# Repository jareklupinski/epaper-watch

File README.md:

# epaper-watch
An epaper watch with a minimalist design and UI

I was working on the breakout board and library for a round epaper display went I accidentally the whole thing.

Oops.

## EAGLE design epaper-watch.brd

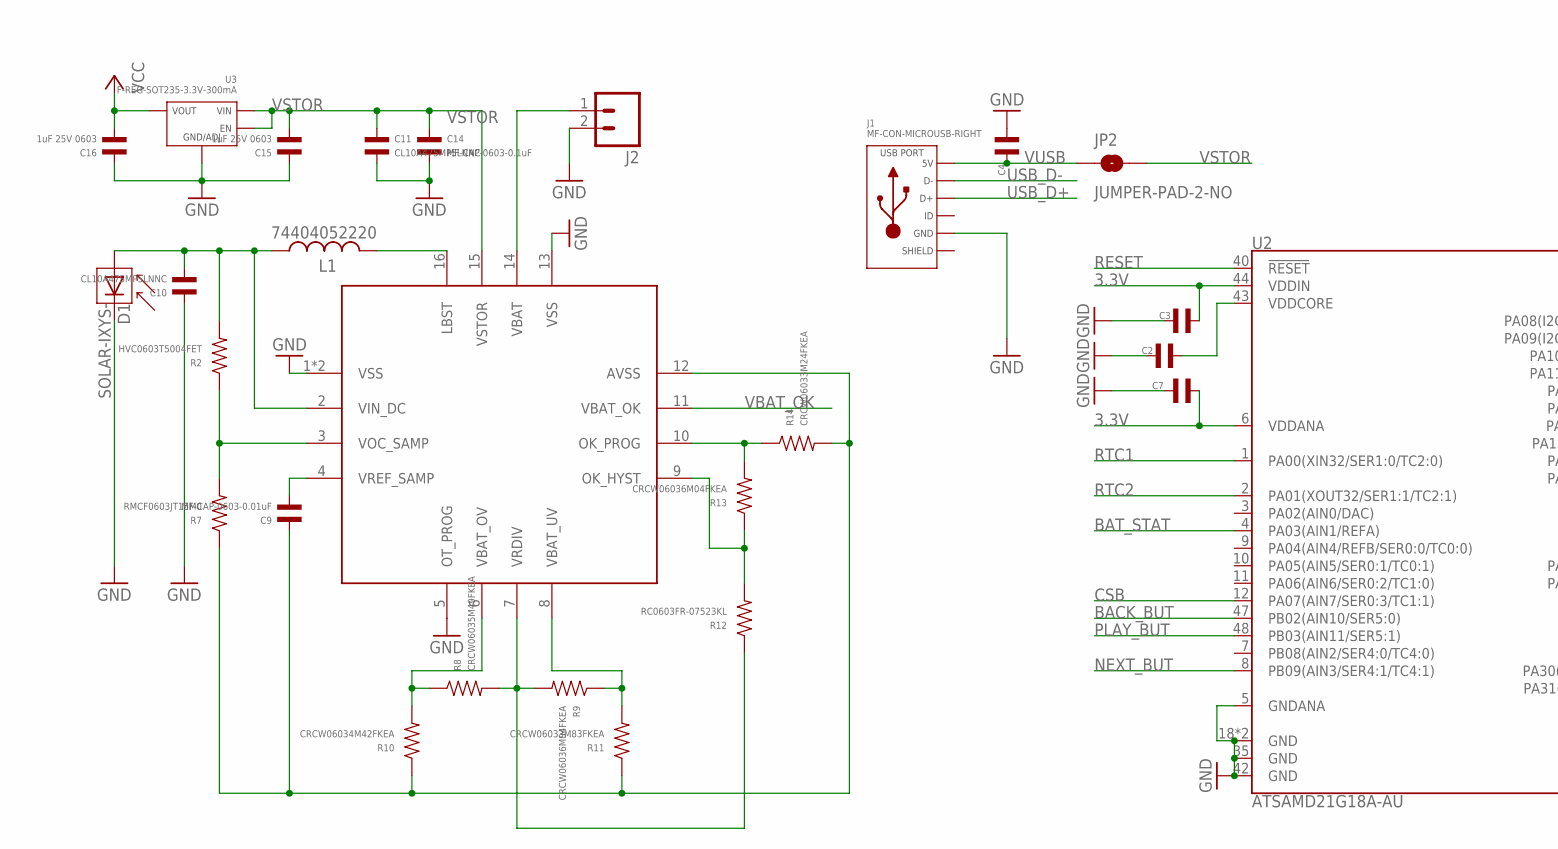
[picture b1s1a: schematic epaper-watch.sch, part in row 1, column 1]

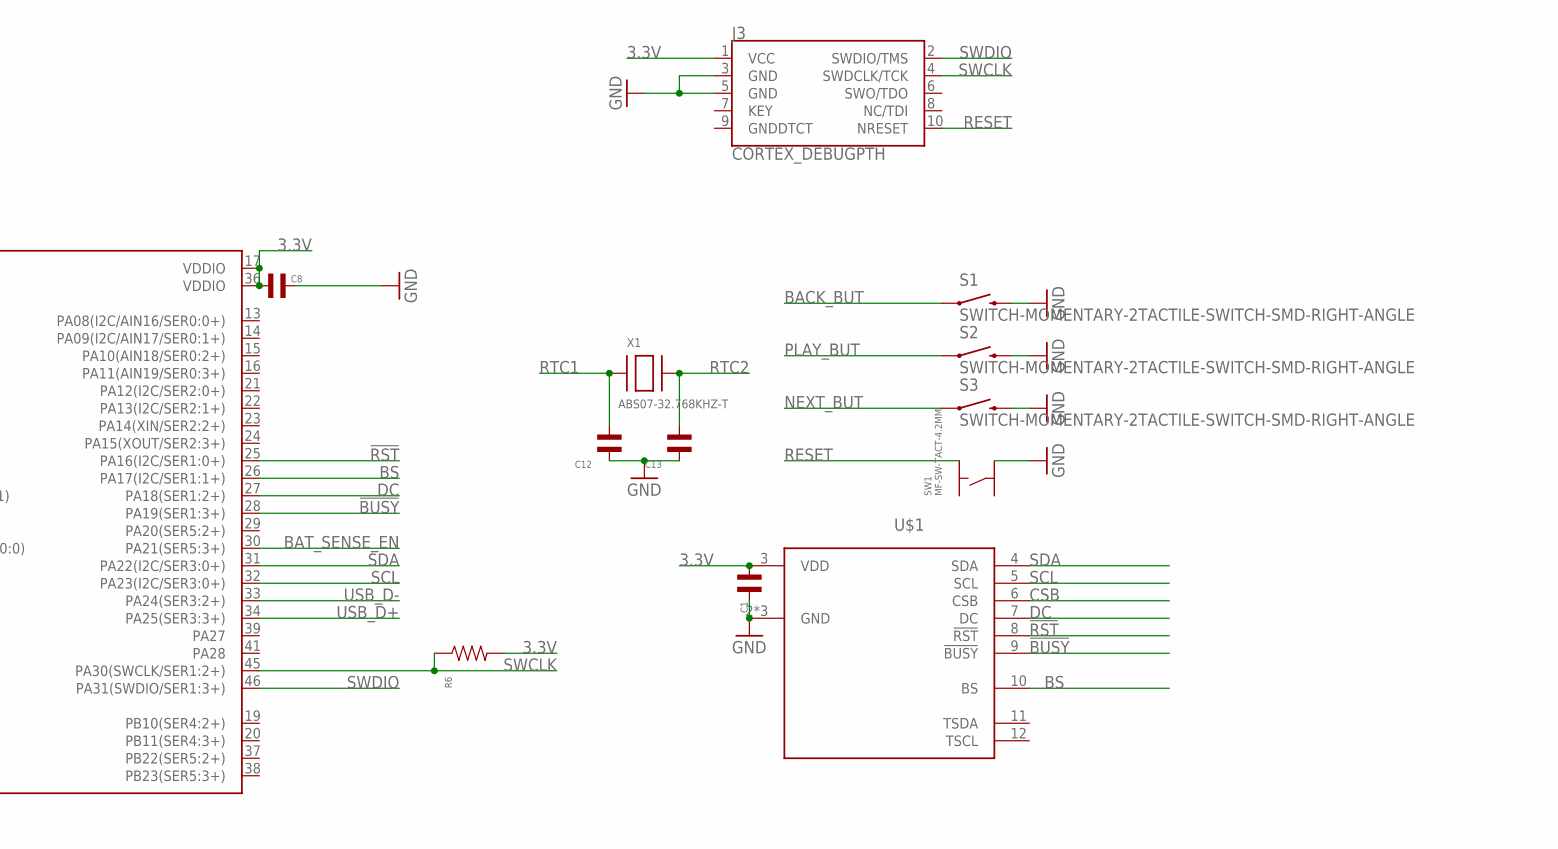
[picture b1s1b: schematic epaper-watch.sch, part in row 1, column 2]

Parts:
C1, C3, C4, C7, C8: 0.1uF 0603; C0603
C2: 1uF 0603; C0603
C9: MF-CAP-0603-0.01uF; C0603
C10, C11: CL10A475MP5LNNC; C0603
C12, C13: 15pF; C0603
C14: MF-CAP-0603-0.1uF; C0603
C15, C16: 1uF 25V 0603; C0603
D1: SOLAR-IXYS-; SOLARBIT-12X1
J1: MF-CON-MICROUSB-RIGHT; MICROUSB-RIGHT
J2: M02PTH; 1X02
J3: CORTEX_DEBUGPTH; 2X5-PTH-1.27MM
JP2: JUMPER-PAD-2-NO; PAD-JUMPER-2-NO_NO_SILK
L1: 74404052220; POWER-CHOKE_WE-TPC
R2: HVC0603T5004FET; R0603
R6: 1K; R0603
R7: RMCF0603JT15M0; R0603
R8: CRCW06035M49FKEA; R0603
R9, R13: CRCW06036M04FKEA; R0603
R10: CRCW06034M42FKEA; R0603
R11: CRCW06033M83FKEA; R0603
R12: RC0603FR-07523KL; R0603
R14: CRCW06033M24FKEA; R0603
S1, S2, S3: SWITCH-MOMENTARY-2TACTILE-SWITCH-SMD-RIGHT-ANGLE; TACTILE_SWITCH-SMD-RIGHT-ANGLE
SW1: MF-SW-TACT-4.2MM; TACT4.2MM
U1: BQ25504RGTT; QFN16-3X3MM_1:1_V03
U2: ATSAMD21G18A-AU; QFN-48
U3: F-REG-SOT235-3.3V-300mA; SOT-23-5
U$1: GDEP011TT2; FH26W-15S-0.3S
X1: ABS07-32.768KHZ-T; XTAL3215

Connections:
3.3V: C1.P$2, C3.P$2, C7.P$2, C8.P$2, J3.1 (VCC), R6.P$2, U2.6 (VDDANA), U2.17 (VDDIO), U2.36 (VDDIO), U2.44 (VDDIN), U$1.3 (VDD)
!BUSY: U2.28 (PA19(SER1:3+)), U$1.9 (!BUSY)
!RST: U2.25 (PA16(I2C/SER1:0+)), U$1.8 (!RST)
BACK_BUT: S1.1, U2.47 (PB02(AIN10/SER5:0))
BAT_SENSE_EN: U2.30 (PA21(SER5:3+))
BAT_STAT: U2.4 (PA03(AIN1/REFA))
BS: U2.26 (PA17(I2C/SER1:1+)), U$1.10 (BS)
CSB: U2.12 (PA07(AIN7/SER0:3/TC1:1)), U$1.6 (CSB)
DC: U2.27 (PA18(SER1:2+)), U$1.7 (DC)
GND: C1.P$1, C2.P$2, C3.P$1, C4.P$2, C7.P$1, C8.P$1, C10.P$1, C11.P$2, C12.P$1, C13.P$1, C14.P$2, C15.P$1, C16.P$1, D1.- (C), J1.5 (GND), J2.2, J3.3 (GND), J3.5 (GND), S1.2, S2.2, S3.2, SW1.P$4, U1.1 (VSS), U1.5 (OT_PROG), U1.13 (VSS), U1.EXT (VSS), U2.5 (GNDANA), U2.18 (GND), U2.35 (GND), U2.42 (GND), U2.EP (GND), U3.P$2 (GND/ADJ), U$1.2 (GND), U$1.EXP1 (GND), U$1.EXP2 (GND)
unnamed: C9.P$2, U1.4 (VREF_SAMP)
unnamed: L1.2, U1.16 (LBST)
unnamed: R12.P$2, R13.P$1, U1.9 (OK_HYST)
unnamed: C9.P$1, R7.P$1, R10.P$1, R11.P$1, R14.P$2, U1.12 (AVSS)
unnamed: C2.P$1, U2.43 (VDDCORE)
unnamed: R13.P$2, R14.P$1, U1.10 (OK_PROG)
unnamed: R8.P$2, R9.P$2, R12.P$1, U1.7 (VRDIV)
unnamed: R9.P$1, R11.P$2, U1.8 (VBAT_UV)
unnamed: R8.P$1, R10.P$2, U1.6 (VBAT_OV)
unnamed: R2.P$1, R7.P$2, U1.3 (VOC_SAMP)
NEXT_BUT: S3.1, U2.8 (PB09(AIN3/SER4:1/TC4:1))
PLAY_BUT: S2.1, U2.48 (PB03(AIN11/SER5:1))
RESET: J3.10 (NRESET), SW1.P$2, U2.40 (!RESET!)
RTC1: C12.P$2, U2.1 (PA00(XIN32/SER1:0/TC2:0)), X1.P$1
RTC2: C13.P$2, U2.2 (PA01(XOUT32/SER1:1/TC2:1)), X1.P$2
SCL: U2.32 (PA23(I2C/SER3:0+)), U$1.5 (SCL)
SDA: U2.31 (PA22(I2C/SER3:0+)), U$1.4 (SDA)
SLD: J1.S1 (SLD)
SOLAR_IN: C10.P$2, D1.+ (A), L1.1, R2.P$2, U1.2 (VIN_DC)
SWCLK: J3.4 (SWDCLK/TCK), R6.P$1, U2.45 (PA30(SWCLK/SER1:2+))
SWDIO: J3.2 (SWDIO/TMS), U2.46 (PA31(SWDIO/SER1:3+))
USB_D+: J1.3 (D+), U2.34 (PA25(SER3:3+))
USB_D-: J1.2 (D-), U2.33 (PA24(SER3:2+))
VBAT: J2.1, U1.14 (VBAT)
VBAT_OK: U1.11 (VBAT_OK)
VCC: C16.P$2, U3.P$5 (VOUT)
VSTOR: C11.P$1, C14.P$1, C15.P$2, JP2.2, U1.15 (VSTOR), U3.P$1 (VIN), U3.P$3 (EN)
VUSB: C4.P$1, J1.1 (5V), JP2.1

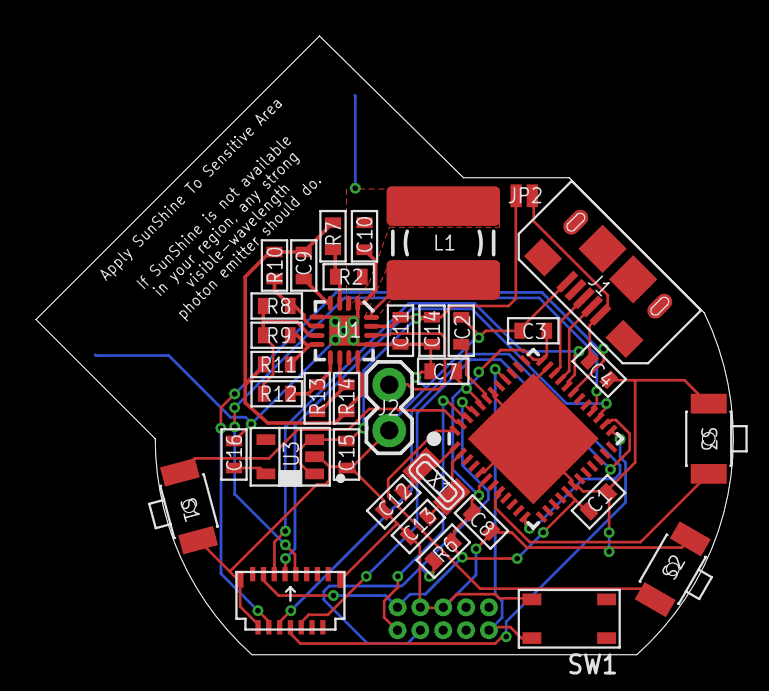
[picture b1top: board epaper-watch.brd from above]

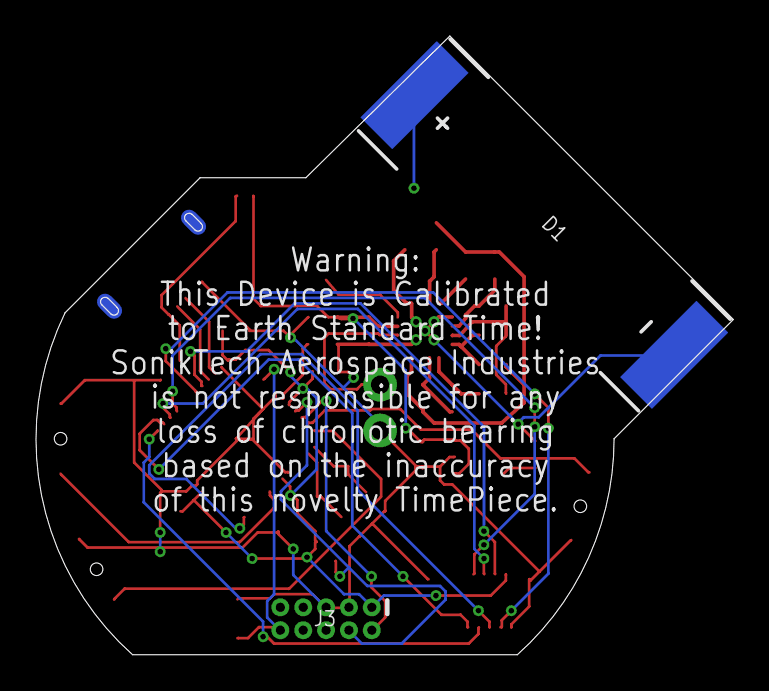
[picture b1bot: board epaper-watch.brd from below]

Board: 2 copper layers, 38.7 x 34.4 mm, 39 parts (2 on the bottom side), 34 nets.

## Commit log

2018-07-05 design tested: partially working

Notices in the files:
parts and their libraries:
SparkFun-Connectors: Licensing: Creative Commons ShareAlike 4.0 International - https://creativecommons.org/licenses/by-sa/4.0
